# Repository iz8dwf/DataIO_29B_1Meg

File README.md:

# DataIO_29B_1Meg
Data I/O 29B 1MB or 512KB board

This board plugs in the bus connector inside the Data I/O 29B device programmer. It provides 1Mbyte RAM storage or 512K if populating only one SRAM IC.
See the image directory before building and installing it. The pin header connector should have at least 50mm pin length to allow enough vertical clearance from the 29B mainboard.

In `gerber_contrib` I've put a contributed PCB version with mounting holes. Original Data I/O expansion was large and heavier and definitely required mounting holes. If you're concerned about board stability you can use the contributed version. My own board didn't move in years of use anyway.

If you have a model 29A (not B), check the other repository.

USE AT YOUR OWN RISK.

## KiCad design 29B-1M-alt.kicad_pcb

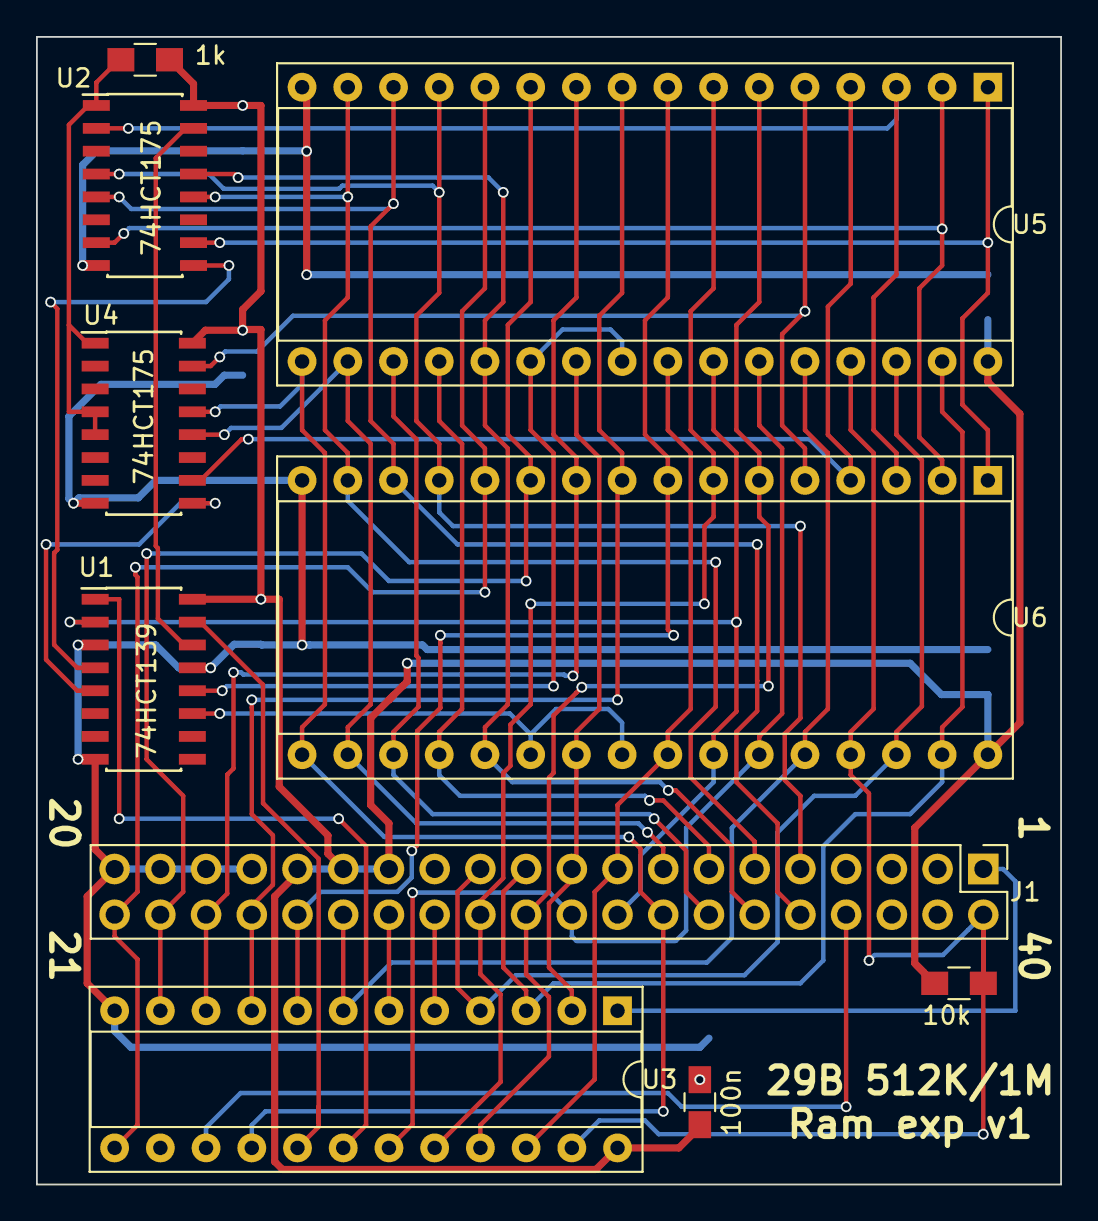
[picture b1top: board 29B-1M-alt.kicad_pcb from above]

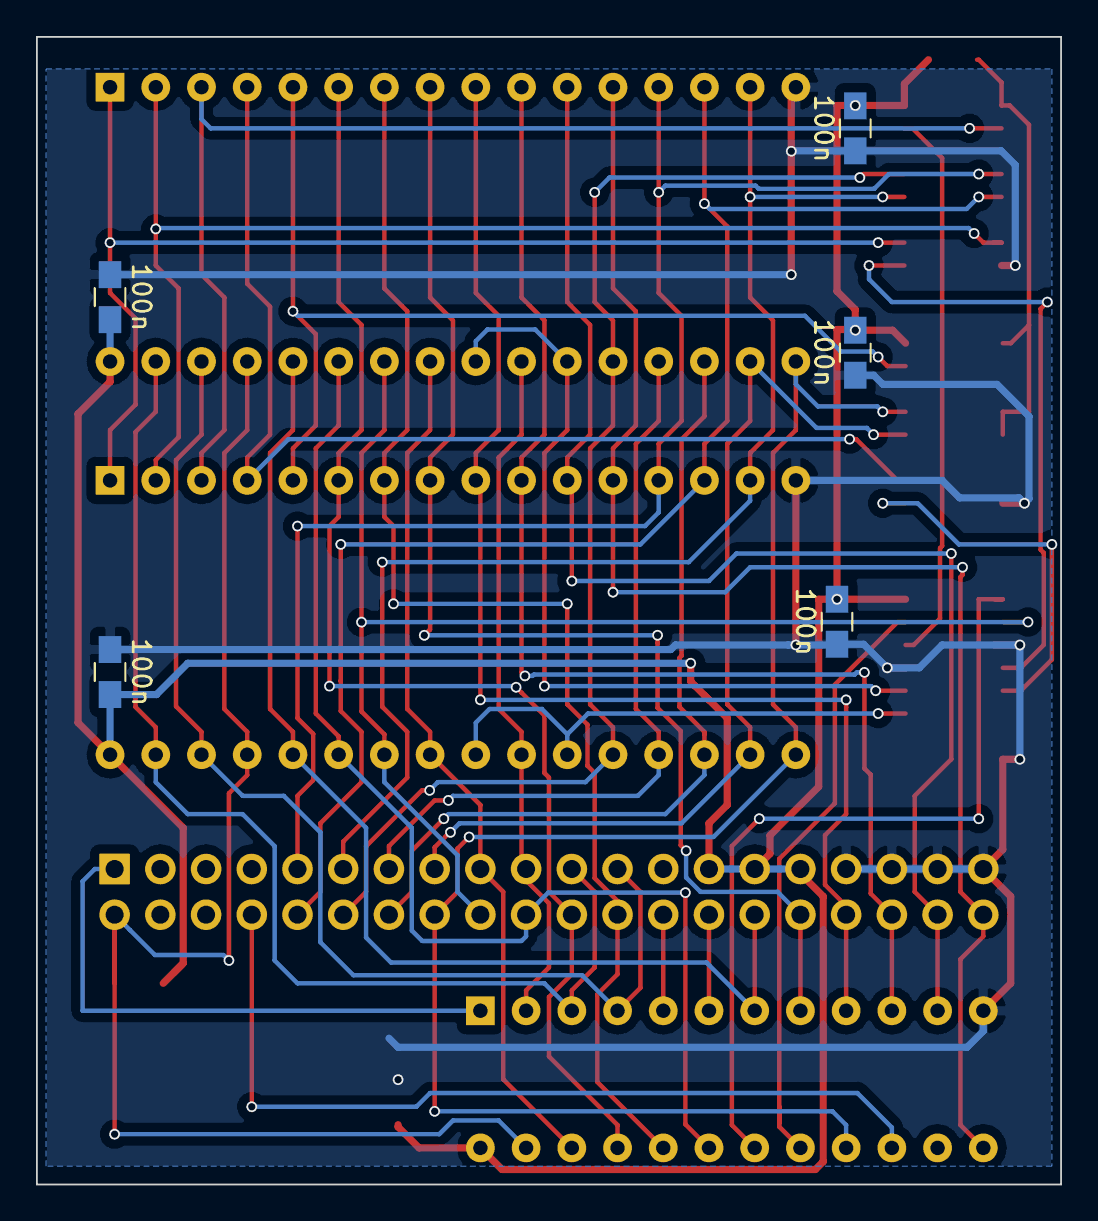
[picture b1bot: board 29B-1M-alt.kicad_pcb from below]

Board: 2 copper layers, 56.9 x 63.8 mm, 15 parts (5 on the bottom side), 42 nets.

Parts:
C1, C2, C3, C4, C5, C6: 100n; C_0805_HandSoldering
J1: Conn_02x20_Odd_Even; Pin_Header_Straight_2x20_Pitch2.54mm
R1: 10k; R_0805_HandSoldering
R2: 1k; R_0805_HandSoldering
U1: 74HCT139; SOIC-16_3.9x9.9mm_Pitch1.27mm
U2, U4: 74HCT175; SOIC-16_3.9x9.9mm_Pitch1.27mm
U3: PAL24; DIP-24_W7.62mm_Socket
U5, U6: SRAM_512Ko; DIP-32_W15.24mm_Socket

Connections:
/A0: J1.18, U1.2, U5.26, U6.26
/A1: J1.17, U3.22, U5.25, U6.25
/A2: J1.20, U3.19, U5.27, U6.27
/A3: J1.19, U3.2, U5.23, U6.23
/A4: J1.22, U3.21, U5.6, U6.6
/A5: J1.21, U3.3, U5.31, U6.31
/A6: J1.24, U3.20, U5.7, U6.7
/A7: J1.23, U3.4, U5.30, U6.30
/A8: J1.40, U3.13, U5.12, U6.12
/A9: J1.38, U3.11, U5.11, U6.11
/A10: J1.36, U3.10, U5.10, U6.10
/A11: J1.34, U3.9, U5.9, U6.9
/A12: J1.32, U3.8, U5.8, U6.8
/A13: J1.30, U3.7, U5.28, U6.28
/A14: J1.28, U3.6
/A15: J1.26, U3.5
/D0: J1.9, U2.4, U5.13, U6.13
/D1: J1.10, U2.5, U5.14, U6.14
/D2: J1.11, U2.12, U5.15, U6.15
/D3: J1.12, U2.13, U5.21, U6.21
/D4: J1.13, U5.20, U6.20
/D5: J1.14, U5.19, U6.19
/D6: J1.15, U4.12, U5.18, U6.18
/D7: J1.16, U3.16, U4.13, U5.17, U6.17
/RA14: U2.2, U5.3, U6.3
/RA15: U2.7, U5.2, U6.2
/RA16: U2.10, U5.1, U6.1
/RA17: U4.15, U5.5, U6.5
/RA18: U4.10, U5.4, U6.4
/~BANK: U1.1, U3.18
/~EN: J1.8, U3.15
/~RAM: U1.15, U3.17
/~V02: J1.1, U3.1
/~WR: J1.2, R1.1, U3.23, U5.29, U6.29
GND: C1.2, C2.2, C3.2, C4.2, C5.2, C6.2, J1.33, J1.35, J1.37, J1.39, U1.3, U1.8, U1.13, U2.8, U3.12, U4.8, U5.16, U6.16
unnamed: R2.1, U2.1, U4.1, U4.4, U4.5
unnamed: U1.4, U2.9
unnamed: U1.5, U4.9
unnamed: U1.11, U6.22, U6.24
unnamed: U1.12, U5.22, U5.24
unnamed: U1.14, U2.15
VCC: C1.1, C2.1, C3.1, C4.1, C5.1, C6.1, J1.27, J1.29, J1.31, R1.2, R2.2, U1.16, U2.16, U3.24, U4.16, U5.32, U6.32

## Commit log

2023-12-19 first upload
2023-12-19 removed unnecessary file
2026-01-04 added contributed gerbers
